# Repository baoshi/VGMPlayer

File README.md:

# VGMPlayer

VGMPlayer players (emulates) Nintendo Entertainment System (NES) / Famicom (FC) game musics.

Introduction video here https://youtu.be/lolSKD4SWRI

Hardware design created using KiCad 7.0, files under hw folder.

Firmware contains "ec" program using PIC16F1503 and "main" program using RP2040, in the respective folder. 

Some design doc can be found in doc folder, but not fully up to date. To better understand the program logic, please refer to HSM implementation at  https://github.com/MadsAndreasen/HierarchicalStateMachine, which of course is further based on Miro Samek's awesome statemachine articles.

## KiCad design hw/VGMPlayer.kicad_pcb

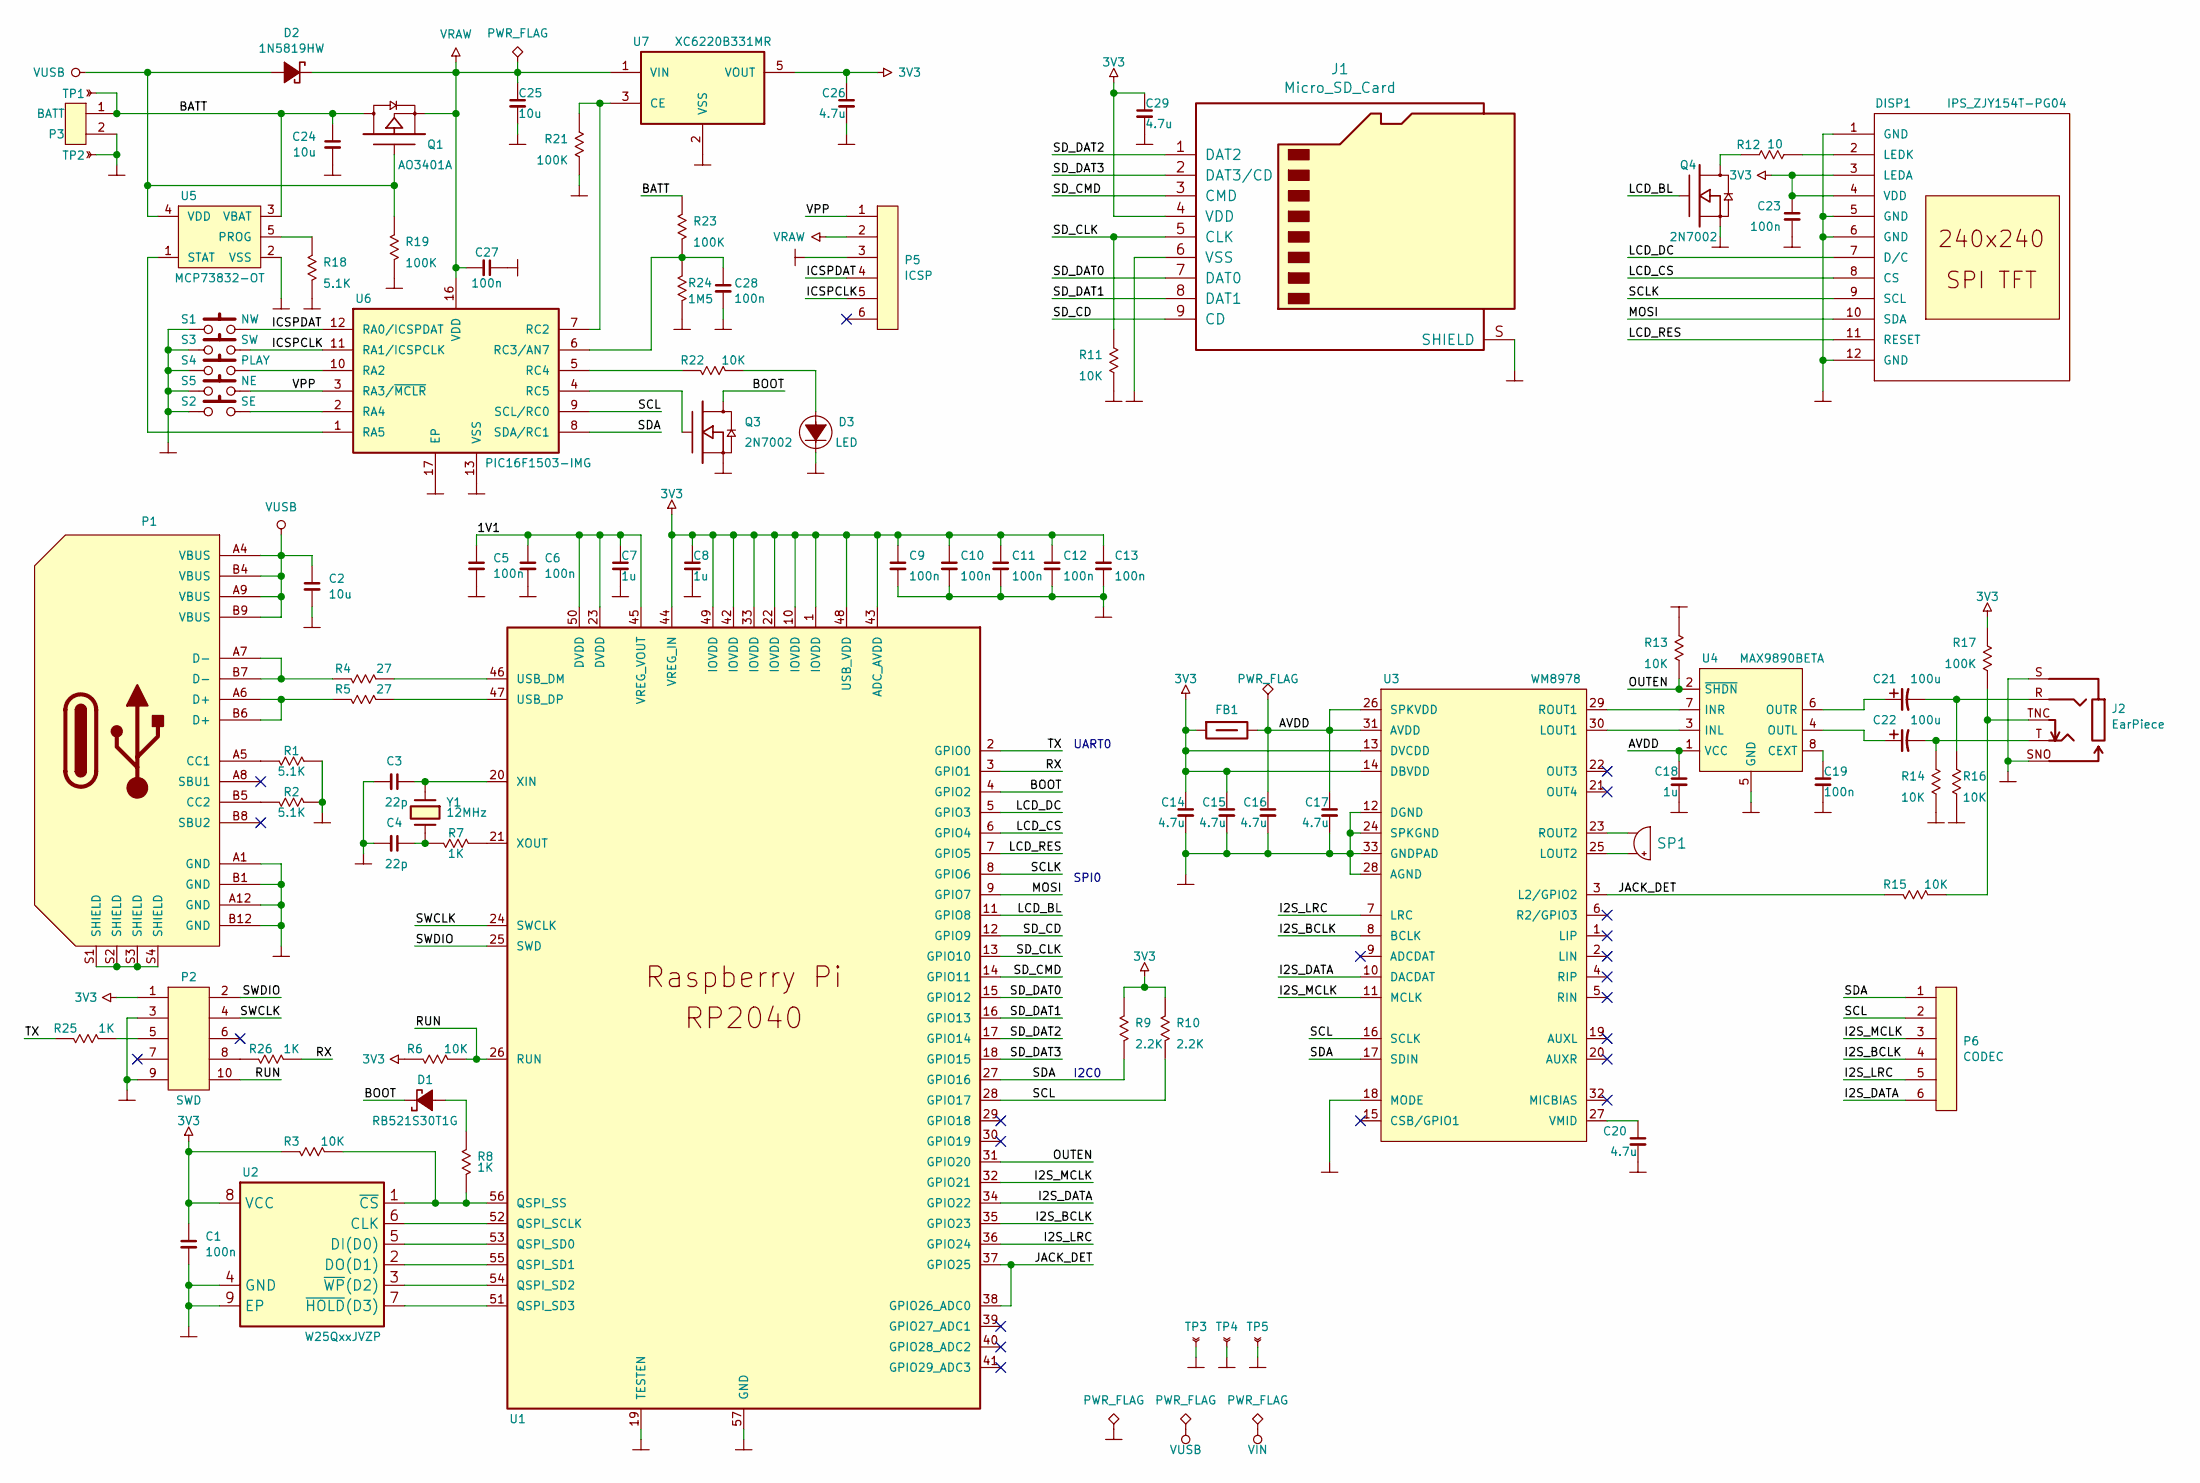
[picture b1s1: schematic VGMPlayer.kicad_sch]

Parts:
C1, C5, C6, C9, C10, C11, C12, C13, C19, C23, C27, C28: 100n; C_0402
C2, C25: 10u; C_0603
C3, C4: 22p; C_0402
C7, C8, C18: 1u; C_0603
C14, C26, C29: 4.7u; C_0603
C15, C16, C17, C20: 4.7u; C_0603; JLCPN C77044
C21, C22: 100u; CP_5x5.3
C24: 10u; C_0603; JLCPN C77044
D1: RB521S30T1G; D_SOD-523
D2: 1N5819HW; D_SOD-123
D3: LED; D_LED_0805_Edge_Lit
DISP1: IPS_ZJY154T-PG04
FB1: FB; L_0805
J1: Micro_SD_Card; XKB_XKTF-015-X
J2: EarPiece; XKB_PJ-327A0-SMT
P1: USB_C_Receptacle_16P; HRO_TYPE-C-31-M-12
P2: SWD; PINHDR-THT-50mil-02x05
P3: BATT; MLX_PicoBlade-Horz-01x02-1.25P
P5: ICSP; PINHDR-THT-50mil-01x06
P6: CODEC; PINHDR-THT-50mil-01x06
Q1: AO3401A; SOT-23-3
Q3, Q4: 2N7002; SOT-523
R1, R2, R18: 5.1K; R_0402
R3, R6, R11, R13, R14, R15, R16, R22: 10K; R_0402
R4, R5: 27; R_0402
R7, R8, R25, R26: 1K; R_0402
R9, R10: 2.2K; R_0402
R12: 10; R_0603
R17, R19, R21, R23: 100K; R_0402
R24: 1M5; R_0402
S1: NW; MultiButton
S2: SE; MultiButton
S3: SW; MultiButton
S4: PLAY; MultiButton
S5: NE; MultiButton
SP1: Speaker; iPhone8Speaker
TP1, TP2, TP3, TP4, TP5: TP; TP_THT-Pad-0.8
U1: RP2040
U2: W25QxxJVZP; WSON-8-1EP_5x6x1.27P_EP4.3x3.4
U3: WM8978; QFN-32-1EP_5x5x0.5P_EP3.45
U4: MAX9890BETA; TDFN-8-1EP_3x3x0.65P_EP2.3x1.5
U5: MCP73832-OT; SOT-23-5
U6: PIC16F1503-IMG; QFN-16-1EP_3x3x0.5P_EP1.1
U7: XC6220B331MR; SOT-23-5
Y1: 12MHz; XTAL_3225_4P

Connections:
3V3: C1.1, C8.1, C9.1, C10.1, C11.1, C12.1, C13.1, C14.1, C15.1, C23.1, C26.1, C29.1, DISP1.3 (LEDA), DISP1.4 (VDD), FB1.2, J1.4 (VDD), P2.1, R3.2, R6.2, R9.1, R10.1, R17.1, U1.1 (IOVDD), U1.10 (IOVDD), U1.22 (IOVDD), U1.33 (IOVDD), U1.42 (IOVDD), U1.43 (ADC_AVDD), U1.44 (VREG_IN), U1.48 (USB_VDD), U1.49 (IOVDD), U2.8 (VCC), U3.13 (DVCDD), U3.14 (DBVDD), U7.5 (VOUT)
/1V1: C5.1, C6.1, C7.1, U1.23 (DVDD), U1.45 (VREG_VOUT), U1.50 (DVDD)
/AVDD: C16.1, C17.1, C18.1, FB1.1, U3.26 (SPKVDD), U3.31 (AVDD), U4.1 (VCC)
/BATT: C24.1, P3.1, Q1.3 (D), R23.1, TP1.1, U5.3 (VBAT)
/BOOT: D1.K, Q3.3 (D), U1.4 (GPIO2)
/I2S_BCLK: P6.4, U1.35 (GPIO23), U3.8 (BCLK)
/I2S_DATA: P6.6, U1.34 (GPIO22), U3.10 (DACDAT)
/I2S_LRC: P6.5, U1.36 (GPIO24), U3.7 (LRC)
/I2S_MCLK: P6.3, U1.32 (GPIO21), U3.11 (MCLK)
/ICSPCLK: P5.5, S3.2, U6.11 (RA1/ICSPCLK)
/ICSPDAT: P5.4, S1.2, U6.12 (RA0/ICSPDAT)
/JACK_DET: R15.2, U1.37 (GPIO25), U1.38 (GPIO26_ADC0), U3.3 (L2/GPIO2)
/LCD_BL: Q4.1 (G), U1.11 (GPIO8)
/LCD_CS: DISP1.8 (CS), U1.6 (GPIO4)
/LCD_DC: DISP1.7 (D/C), U1.5 (GPIO3)
/LCD_RES: DISP1.11 (RESET), U1.7 (GPIO5)
/MOSI: DISP1.10 (SDA), U1.9 (GPIO7)
/OUTEN: R13.2, U1.31 (GPIO20), U4.2 (~SHDN)
/RUN: P2.10, R6.1, U1.26 (RUN)
/RX: R26.1, U1.3 (GPIO1)
/SCL: P6.2, R10.2, U1.28 (GPIO17), U3.16 (SCLK), U6.9 (SCL/RC0)
/SCLK: DISP1.9 (SCL), U1.8 (GPIO6)
/SDA: P6.1, R9.2, U1.27 (GPIO16), U3.17 (SDIN), U6.8 (SDA/RC1)
/SD_CD: J1.9 (CD), U1.12 (GPIO9)
/SD_CLK: J1.5 (CLK), R11.1, U1.13 (GPIO10)
/SD_CMD: J1.3 (CMD), U1.14 (GPIO11)
/SD_DAT0: J1.7 (DAT0), U1.15 (GPIO12)
/SD_DAT1: J1.8 (DAT1), U1.16 (GPIO13)
/SD_DAT2: J1.1 (DAT2), U1.17 (GPIO14)
/SD_DAT3: J1.2 (DAT3/CD), U1.18 (GPIO15)
/SWCLK: P2.4, U1.24 (SWCLK)
/SWDIO: P2.2, U1.25 (SWD)
/TX: R25.2, U1.2 (GPIO0)
/VPP: P5.1, S5.2, U6.3 (RA3/~MCLR)
GND: C1.2, C2.2, C3.2, C4.2, C5.2, C6.2, C7.2, C8.2, C9.2, C10.2, C11.2, C12.2, C13.2, C14.2, C15.2, C16.2, C17.2, C18.2, C19.2, C20.2, C23.2, C24.2, C25.2, C26.2, C27.1, C28.2, C29.2, D3.K, DISP1.1 (GND), DISP1.5 (GND), DISP1.6 (GND), DISP1.12 (GND), J1.6 (VSS), J1.S (SHIELD), J2.S, J2.SNO, P1.A1 (GND), P1.A12 (GND), P1.B1 (GND), P1.B12 (GND), P2.3, P2.9, P3.2, P5.3, Q3.2 (S), Q4.2 (S), R1.1, R2.1, R11.2, R13.1, R14.2, R16.2, R18.2, R19.2, R21.2, R24.2, S1.1, S2.1, S3.1, S4.1, S5.1, TP2.1, TP3.1, TP4.1, TP5.1, U1.19 (TESTEN), U1.57 (GND), U2.4 (GND), U2.9 (EP), U3.12 (DGND), U3.18 (MODE), U3.24 (SPKGND), U3.28 (AGND), U3.33 (GNDPAD), U4.5 (GND), U4.9 (GND), U5.2 (VSS), U6.13 (VSS), U6.17 (EP), U7.2 (VSS)
unnamed: C3.1, U1.20 (XIN), Y1.1 (OSC1)
unnamed: C4.1, R7.2, Y1.3 (OSC2)
unnamed: C19.1, U4.8 (CEXT)
unnamed: C20.1, U3.27 (VMID)
unnamed: C21.1, U4.6 (OUTR)
unnamed: C21.2, J2.R, R16.1
unnamed: C22.1, U4.4 (OUTL)
unnamed: C22.2, J2.T, R14.1
unnamed: C28.1, R23.2, R24.1, U6.6 (RC3/AN7)
unnamed: D1.A, R8.1
unnamed: D3.A, R22.2
unnamed: DISP1.2 (LEDK), R12.1
unnamed: J2.TNC, R15.1, R17.2
unnamed: P1.A5 (CC1), R1.2
unnamed: P1.A6 (D+), P1.B6 (D+), R5.2
unnamed: P1.A7 (D-), P1.B7 (D-), R4.2
unnamed: P1.B5 (CC2), R2.2
unnamed: P1.S1 (SHIELD), P1.S2 (SHIELD), P1.S3 (SHIELD), P1.S4 (SHIELD)
unnamed: P2.5, R25.1
unnamed: P2.8, R26.2
unnamed: Q3.1 (G), U6.4 (RC5)
unnamed: Q4.3 (D), R12.2
unnamed: R3.1, R8.2, U1.56 (QSPI_SS), U2.1 (~CS)
unnamed: R4.1, U1.46 (USB_DM)
unnamed: R5.1, U1.47 (USB_DP)
unnamed: R7.1, U1.21 (XOUT)
unnamed: R18.1, U5.5 (PROG)
unnamed: R21.1, U6.7 (RC2), U7.3 (CE)
unnamed: R22.1, U6.5 (RC4)
unnamed: S2.2, U6.2 (RA4)
unnamed: S4.2, U6.10 (RA2)
unnamed: SP1.1, U3.25 (LOUT2)
unnamed: SP1.2, U3.23 (ROUT2)
unnamed: U1.51 (QSPI_SD3), U2.7 (~HOLD(D3))
unnamed: U1.52 (QSPI_SCLK), U2.6 (CLK)
unnamed: U1.53 (QSPI_SD0), U2.5 (DI(D0))
unnamed: U1.54 (QSPI_SD2), U2.3 (~WP(D2))
unnamed: U1.55 (QSPI_SD1), U2.2 (DO(D1))
unnamed: U3.29 (ROUT1), U4.7 (INR)
unnamed: U3.30 (LOUT1), U4.3 (INL)
unnamed: U5.1 (STAT), U6.1 (RA5)
VRAW: C25.1, C27.2, D2.K, P5.2, Q1.2 (S), U6.16 (VDD), U7.1 (VIN)
VUSB: C2.1, D2.A, P1.A4 (VBUS), P1.A9 (VBUS), P1.B4 (VBUS), P1.B9 (VBUS), Q1.1 (G), R19.1, U5.4 (VDD)

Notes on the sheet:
UART0
SPI0
I2C0

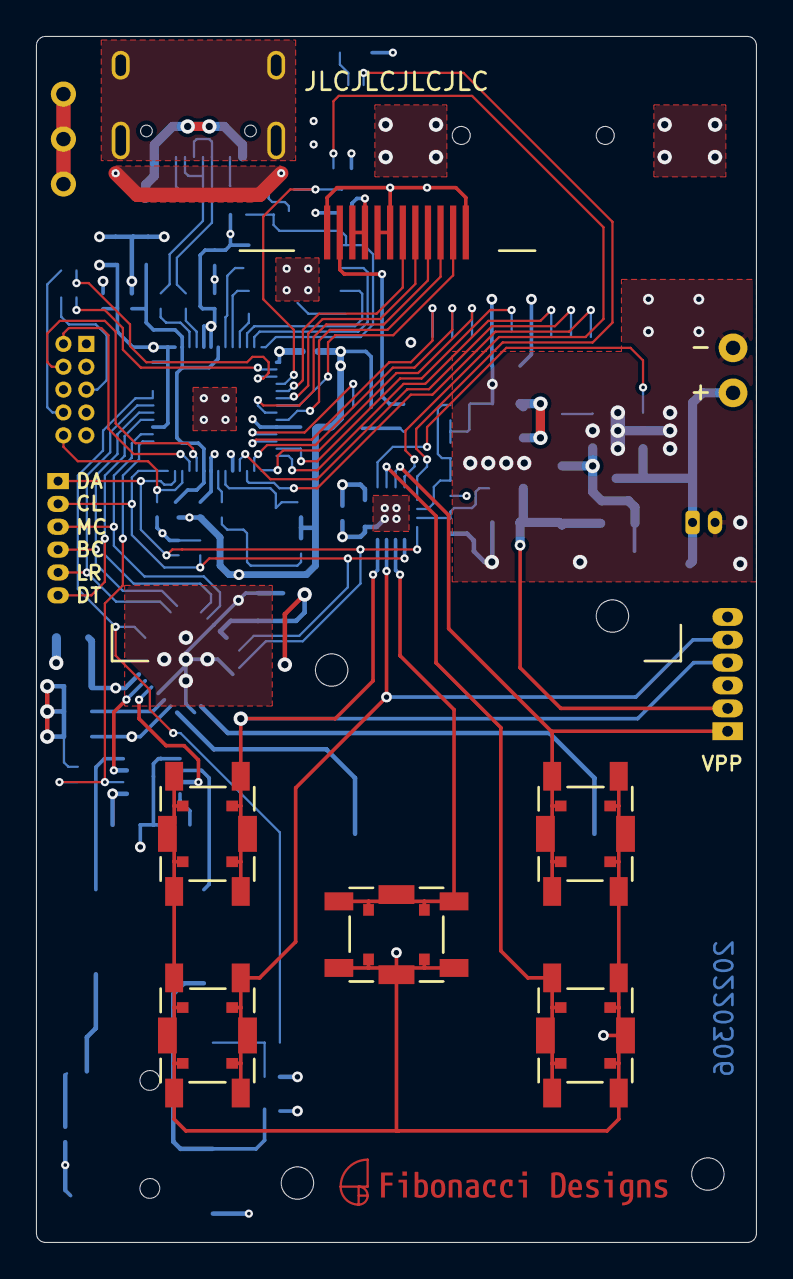
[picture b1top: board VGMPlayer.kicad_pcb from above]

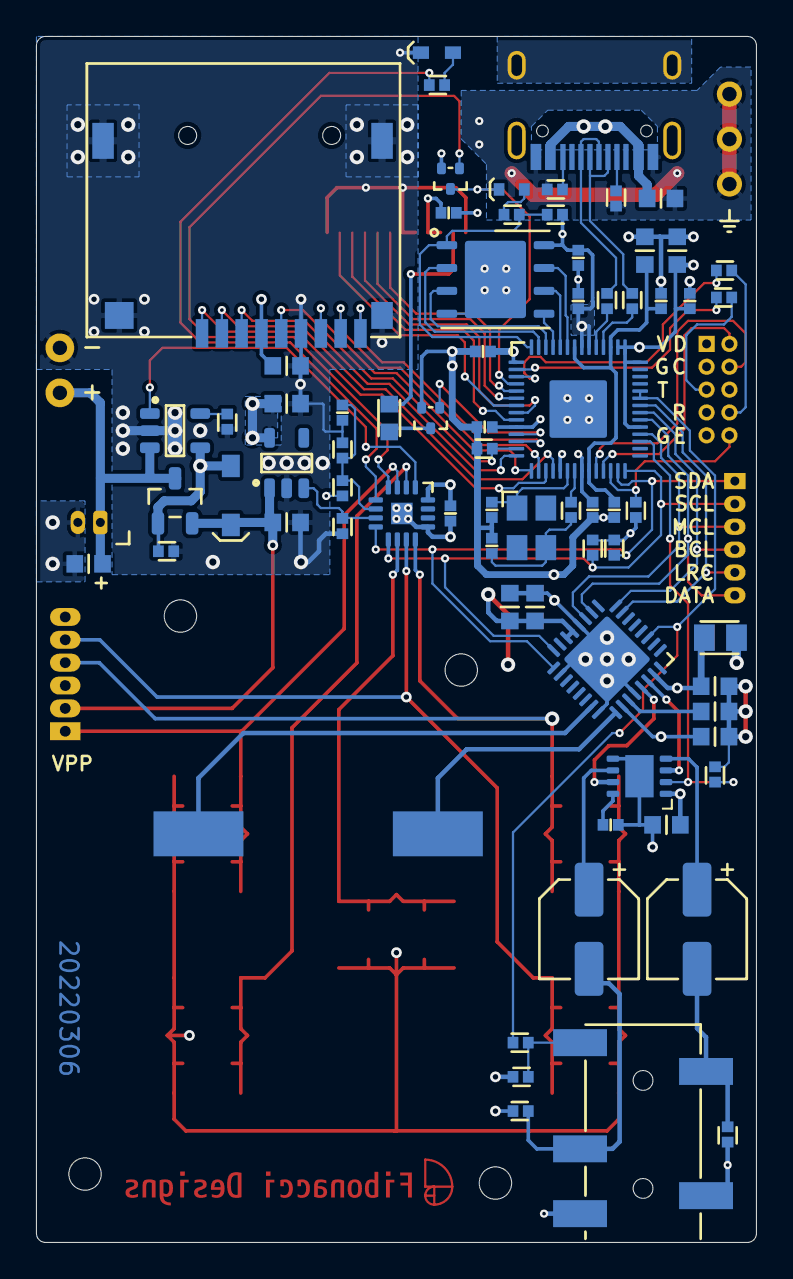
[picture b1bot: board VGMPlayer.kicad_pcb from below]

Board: 4 copper layers, 40.0 x 67.0 mm, 89 parts (82 on the bottom side), 78 nets.

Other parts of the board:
kibuzzard-62236962: G***; kibuzzard-62236962

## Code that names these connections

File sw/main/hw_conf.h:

#ifndef HW_CONFIG_H
#define HW_CONFIG_H

#include <stdbool.h>

//
// Pin Config
//

// SD Card
#define SDCARD_SPI_INST         spi1
#define SDCARD_CLK_PIN          10
#define SDCARD_CMD_PIN          11
#define SDCARD_DAT0_PIN         12
#define SDCARD_DAT1_PIN         13
#define SDCARD_DAT2_PIN         14
#define SDCARD_DAT3_PIN         15
#define SDCARD_CD_PIN           9
// SD Card in SPI mode
#define SDCARD_SPI_MOSI_PIN     SDCARD_CMD_PIN
#define SDCARD_SPI_MISO_PIN     SDCARD_DAT0_PIN
#define SDCARD_SPI_CS_PIN       SDCARD_DAT3_PIN
#define SDCARD_SPI_CLK_PIN      SDCARD_CLK_PIN

// ST7789 LCD
#define ST7789_SPI_INST         spi0
#define ST7789_CLK_PIN          6
#define ST7789_MOSI_PIN         7
#define ST7789_CS_PIN           4
#define ST7789_DC_PIN           3
#define ST7789_RST_PIN          5
#define ST7789_DMA_IRQ          DMA_IRQ_0
#define ST7789_DMA_INTS         ints0
// Check RP2040 Datasheet for slice and channel for PWM
#define ST7789_BCKL_PIN         8
#define ST7789_BCKL_PWM_SLICE   4
#define ST7789_BCKL_PWM_CHANNEL PWM_CHAN_A

// I2C bus shared with embedded controller (ec) and WM8978
#define I2C_INST        i2c0
#define I2C_SDA_PIN     16
#define I2C_SCL_PIN     17
#define I2C_TIMEOUT_US  1000
#define I2C_BAUD_HZ     (400 * 1000)

// AUDIO
#define I2S_DATAOUT_PIN         22
#define I2S_BCLK_PIN            23
#define I2S_LRC_PIN             24
#define I2S_MCLK_PIN            21
#define I2S_PIO                 pio0            // Use pio0 for I2S
#define I2S_PIO_SM              0               // Use statement machine 0
#define I2S_DMA_IRQ             DMA_IRQ_1
#define I2S_DMA_INTS            ints1
#define JACK_OUTEN_PIN          20              // Audio jack output enable (active high), controls MAX9090B
#define JACK_DETECTION_PIN      25              // Jack detection, high when jack inserted
#define JACK_DETECTION_ADC_PIN  26              // Backup jack detection using ADC

//
// DMA channel allocation
//
#define DMA_CHANNEL_I2S_TX          0
#define DMA_CHANNEL_SDCARD_SPI_TX   1
#define DMA_CHANNEL_SDCARD_SPI_RX   2
#define DMA_CHANNEL_ST7789_SPI_TX   3
#define DMA_CHANNEL_ST7789_SPI_RX   4



#ifdef __cplusplus
extern "C"
{
#endif

bool i2c_lock();
void i2c_unlock();

void hw_shared_resource_init();


#ifdef __cplusplus
}
#endif

#endif

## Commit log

2021-05-17 Initial hw commit
2021-06-07 2nd version, change KBC functions
2021-06-07 Add KPC software flowchart
2021-06-07 Using Molex Picoblade 1.25 connector
2021-06-08 Fix wrong 2N7002 pinout
2021-06-09 USB/Batt power path
2021-06-10 Checkin before fab 20210610
2021-06-10 Sent for fab 20210610
2021-06-24 Change to 4 buttons, layout adjust to casing design
2021-06-26 Archive files sent to factory
2021-06-27 Change 2N7002 footprint to SOT-523
2021-06-27 Fix SWD connector orientation
2021-06-27 Remove SD card bypass capacitor (very close to main filter cap)
2021-07-01 Initial commit of EC code
2021-07-01 begin FSM implementation
2021-07-01 sleep current testing
2021-07-03 Use LPBOR in sleep mode and BOR in normal mode
2021-07-04 Add analog power selection jumper and multiple button options
2021-07-05 more pcb editing
2021-07-05 WIP sleep state change
2021-07-05 Tick timing measurement and change
2021-07-05 States reorg
2021-07-05 More state machine including LED
2021-07-11 Implement Pre-DFU state
2021-07-11 MISRA compatibility
2021-07-12 Implement MAINLOOP and OFF states
2021-07-12 Fix LCD wiring
2021-07-14 Further layout optimize
2021-07-14 Tag for Fab-20210714
2021-07-15 Rename button labels
2021-08-06 Wakeup only check button down
2021-08-10 Adjust USB detection threshold
2021-08-10 change uplink data format
2022-02-07 Using Linux Kicad 6.0.1
2022-02-07 Upgrade KiCad 6.0.1 Linux
2022-02-17 Ignore backups
2022-02-17 Add some documentation
2022-02-17 Adding main firmware
2022-02-17 Add umm_malloc
2022-02-17 Add event
2022-02-17 Remove testing code
2022-02-18 Add tick
2022-02-18 fix event queue using spin lock
2022-02-19 Add EC
2022-02-19 Add backlight
2022-02-19 Add backlight dimming
2022-02-19 Move backlight idle stuff into backlight module
2022-02-19 Backlight timing change
2022-02-19 Add font
2022-02-20 move ec, backlight into modules
2022-02-20 Add disk system
2022-02-20 Change xxx_update return type
2022-02-20 adjust startuip timing
2022-02-21 Add browser hsm
2022-02-22 add status display
2022-02-22 Testing WM8978
2022-02-22 move status update to browser state
2022-02-22 wip wm8978
2022-02-22 WIP: New WM8978 driver
2022-02-23 Testing rockbox wm8978 driver
2022-02-23 fix browser state starts into nodisk state
2022-02-23 remove repeated same message in the queue
2022-02-24 update event queue system to use double link list and mergable messages
2022-02-24 Testing jack detection
2022-02-24 Enable OUT1 and OUT2 for jack detection to work
2022-02-24 Unset VROI and set 5K VID impedance reduces pop
2022-02-25 add mode button navigation in browser_disk
2022-02-26 Adding player state
2022-02-26 add i2s
2022-02-27 wip / adding decoder interface
2022-02-27 add sample decoder
2022-02-27 Playback stop / restart fixing
2022-02-28 fix play reentry
2022-02-28 audio ramp up/down pause/unpause
2022-03-01 add decoder_s16
2022-03-01 Handling play/pause/exit
2022-03-03 V4 hardware
2022-03-06 V4 hardware send for JLC
2022-04-03 MCP73831->MCP83832
2022-04-07 Use new iPhone8 measurement
2022-05-10 Add new EC (5 buttons) code with tester
2022-05-10 Temporary disable i2c activity tracker
2022-05-10 Modify I2C data0 bits
2022-05-10 Ignore .DS_Store
2022-05-11 Update docs. Code cleanup
2022-05-12 Update comments
2022-05-12 Change to 5 buttons
2022-05-12 update buttons
2022-05-12 Fix jack detection gpio/adc error
2022-05-12 Adding UI design
2022-05-14 WIP, changing file list algorithm
2022-05-23 Add EC watchdog on/off command
2022-05-23 Move EC and FileSys tests to tester
2022-05-23 Add timing for ls and lister
2022-05-23 Update lvgl from upstream
2022-05-23 Migrate fatfs settings from fsdev to main
2022-05-25 WIP integrating lister into main
2022-05-28 more implementation of browser state
2022-05-30 Add browse folder history
2022-05-31 Add "get next" for lister and long file name behavior
2022-06-09 Move browser status to lister object
2022-06-13 Move lister as global object
2022-06-13 Type for path
2022-06-13 Add loading message
2022-06-13 update font generator
2022-06-13 Update bdf2lvgl
2022-06-14 Update symbol
2022-06-14 Selection history is now index in catalog file
2022-06-16 Add lister next/prev navigation
2022-06-17 add lister cache
2022-06-18 WIP cleanup lister
2022-06-18 Improve lister implementation
2022-06-18 fix last entry index error
2022-06-18 fix empty directory bug
2022-06-19 simplify lister
2022-06-19 Rename lister to catalog
2022-06-19 wip: player exception state
2022-06-20 rename time to timer
2022-06-20 add alert message timeout
2022-06-20 Cleanup theme
2022-06-20 Add theme color variables
2022-06-20 message box themed
2022-06-20 implement prev/next song with event
2022-06-22 Update design
2022-06-24 Implement new player key bindings
2022-06-24 differenciate eof and fserr
2022-06-25 Add brightness popup
2022-06-26 use dynamic sub-state
2022-06-26 working dynamic setting state
2022-06-26 Modified HSM. When event was handled by higher state in the hierarchy, and transition appens, transit happs from current state instead of higher state.
2022-06-26 sync player to use setting state
2022-06-26 Use single callback for h/w buttons
2022-06-27 wip refactor browser
2022-06-27 refactoring browser
2022-06-27 always calculate LCA due to dynamic states
2022-06-27 remap->map
2022-06-27 no catalog cleanup if transit to player
2022-06-28 Add simulated EEPROM section
2022-06-30 Add eeprom
2022-07-01 Add i2c soft reset to prevent EC bad state
2022-07-02 Modify Theme
2022-07-02 impove empty folder handling
2022-07-02 Add brightness setting
2022-07-02 Add settings box style
2022-07-02 restructure style and theme
2022-07-03 move more styles to lvstyle.c
2022-07-03 unify img resource naming, add custom style to file list
2022-07-03 Add brightness alpha icon
2022-07-03 Better theming
2022-07-17 Add set_volume
2022-07-17 Improve comments
2022-07-17 settings->setting
2022-07-17 clean up setting
2022-07-18 Format and typo
2022-07-18 more comments
2022-07-18 add comments
2022-07-18 add jack detection
2022-07-18 Modify card detection as jack detection
2022-07-18 Add audio init
2022-07-18 Disable jack at start
2022-07-18 add config and load/save
2022-07-19 cleanup
2022-07-19 WIP Alert box
2022-07-19 WIP add alert and change input enable/disable
2022-07-21 WIP add input
2022-07-21 Modifyed browser and setting to use input
2022-07-21 Add slider box and use slider for brightness
2022-07-22 Use input on player
2022-07-22 Use input in alert
2022-07-22 Add HSM change explaination
2022-07-23 Completely removed lvinput
2022-07-23 Add pageup/down icon
2022-07-23 prelimiary audio playback working
2022-07-23 WIP more flexible input event mapping
2022-07-24 WIP input change
2022-07-24 Implementing input setup
2022-07-24 export/import input config for popups
2022-07-24 modify input for setting
2022-07-25 auto advance in player
2022-07-26 navigation working. add silence after playback
2022-07-26 Move start playing to entry
2022-07-26 Let state manage own input group
2022-07-26 better naming input save / load
2022-07-28 remove dynamic states
2022-07-28 Move alert to popup mechanism
2022-07-28 Remove all dynamic state stuff
2022-07-28 Update inputs
2022-07-28 update state digram
2022-07-29 Add volume popup icons
2022-07-29 remove unused file
2022-07-31 Clean up and add documents
2022-07-31 improve volume popup
2022-08-01 save setting, fix audio ramp bug
2022-08-02 Add auto close to volume and brightness popup
2022-08-02 Notify player for sample ready
2022-08-02 Add nsf module
2022-08-04 remove nsf module
2022-08-04 Add nsfc as submodule
2022-08-04 add missing header
2022-08-04 fix compiling warnings
2022-08-04 move buffer to stack
2022-08-04 Testing nsfc interface
2022-08-04 testing nsfc
2022-08-19 Remove nsfc
2022-08-19 add vgmdec
2022-08-19 Initial support VGM
2022-08-19 update vgmdec
2022-08-20 ignore
2022-08-20 Differenciate song finish/terminate
2022-08-20 WIP performance check
2022-08-21 remove DMA ISR in ST7789
2022-08-24 wip trouble shooting performace issue
2022-08-25 wip, use block ram
2022-08-25 Removed vgmdec
2022-08-26 implement dfreader
2022-08-26 implement pause/resume/back in player
2022-08-27 move decoders into audio module
2022-08-27 Update vgmcore, add vgm playback
2022-08-27 Use fifo for comm, fix card eject playback error
2022-08-27 fix auto play next song fail
2022-08-28 Increase audio frame length
2022-08-28 remove vgmcore
2022-08-28 Removed vgmcore
2022-08-28 Correct vgmcore url
2022-08-29 Add audio progress report
2022-08-29 move s16->u32 conversion to audio module
2022-08-29 add sampling buffer
2022-08-29 testing fft
2022-08-30 test adding spectrum display
2022-08-31 remove logarithmic spectrum scale
2022-08-31 fix spectrum overflow
2022-09-02 Temporary remove lvgl for update
2022-09-02 Add lvgl back from local repo
2022-09-03 wip spectrum
2022-09-03 fix spectrum range
2022-09-03 update spectrum with utility
2022-09-04 Add styles for spetrum
2022-09-04 UI experimenting
2022-09-04 testing battery icon
2022-09-05 add battery monitor in top state
2022-09-05 update browser layout
2022-09-05 Shink images
2022-09-05 remove unused lvgl objects
2022-09-05 Get back ST7789 DMA
2022-09-05 cleanup unused code
2022-09-05 fix eject when playing and insert card list empty
2022-09-06 player now continue on alert or exit if alert on first song
2022-09-06 update player layout
2022-09-06 Update icons
2022-09-06 update layout and add player icon
2022-09-06 add progress bar
2022-09-08 move all asset to lvassets.h, update lvgl 8.3.1
2022-09-08 Update UI
2022-09-08 add vgz2vgm, add file pattern filter
2022-09-09 sync vgmcore
2022-09-09 update layout
2022-09-10 track master vgmcore
2022-09-10 fix top label size problem
2022-09-26 WIP Add thumbnail
2022-09-26 Add thumbnail display
2022-09-27 change thumb nane
2022-09-29 handle vgm creation error
2022-09-29 Change Keymap
2022-09-30 Update switch names
2022-10-01 Set EC to PROD mode
2022-10-01 Enable watchdog
2022-10-01 Add power off function
2022-10-01 Move display dimming and auto off to powerman
2022-10-01 move handle for auto-off to top state
2022-10-08 Set board thickness to 1mm
2023-02-13 Save with KiCad 7.0
2023-03-17 solve build error in linux
2023-03-19 Cleanup for upload
2023-03-19 Remove lvgl temporary
2023-03-19 Update lvgl submodule to track github repo
